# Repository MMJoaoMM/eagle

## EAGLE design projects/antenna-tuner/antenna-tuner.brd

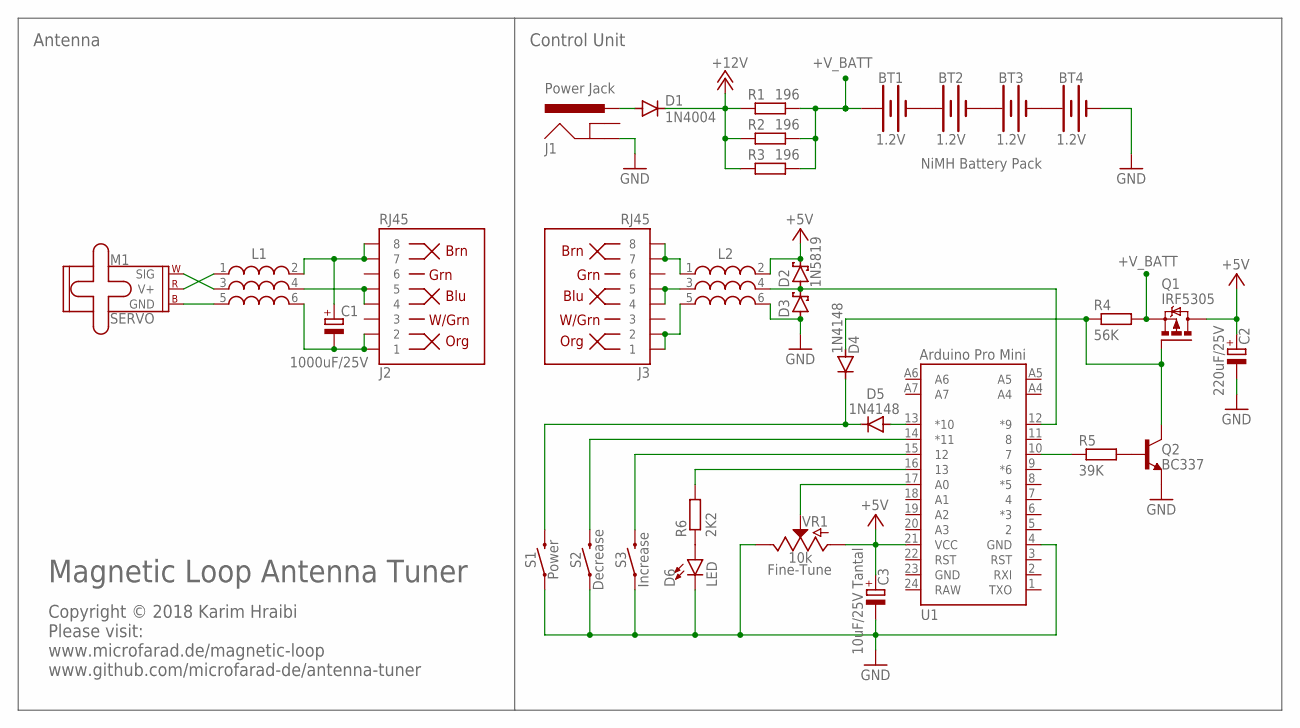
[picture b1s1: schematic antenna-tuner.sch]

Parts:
BT1, BT2, BT3, BT4: 1.2V; BATTERY-AA
C1: 1000uF/25V; E5-10,5
C2: 220uF/25V; E2,5-6
C3: 10uF/25V Tantal; E2,5-6
D1: 1N4004; DO41-10
D2, D3: 1N5819; DO41-7.6
D4, D5: 1N4148; DO35-7
D6: LED; LED_5MM
J1: Power Jack; POWER_JACK_PTH_BREAD
J2, J3: RJ45; RJ45-8
L1, L2: WE-MLS-3WAY_74273001; WE-3WAY_74273001
M1: SERVO; 1X03
Q1: IRF5305; TO220V
Q2: BC337; TO92
R1, R2, R3: 196; 0207/7
R4: 56K; 0207/7
R5: 39K; 0207/7
R6: 2K2; 0207/7
S1: Power; TACTILE_SWITCH_PTH_6.0MM
S2: Decrease; TACTILE_SWITCH_PTH_6.0MM
S3: Increase; TACTILE_SWITCH_PTH_6.0MM
U1: Arduino Pro Mini; ARDUINO_PRO_MINI_TS
VR1: 10k; POT-PTH-ALPS

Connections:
+5V: C2.+, C3.+, D2.C, L2.2, Q1.2, U1.21 (VCC), VR1.P$3 (A)
+12V: D1.C, R1.1, R2.1, R3.1
+V_BATT: BT1.PWR@1 (+), Q1.3, R1.2, R2.2, R3.2, R4.2
GND: BT4.GND@1 (-), C2.-, C3.-, D3.A, D6.K (C), J1.GND, L2.6, Q2.1 (E), S1.1, S2.1, S3.1, U1.4 (GND), U1.23 (GND), VR1.P$1 (E)
unnamed: D1.A, J1.PWR
unnamed: BT1.GND@1 (-), BT2.PWR@1 (+)
unnamed: BT3.GND@1 (-), BT4.PWR@1 (+)
unnamed: BT2.GND@1 (-), BT3.PWR@1 (+)
unnamed: U1.17 (A0), VR1.P$2 (S)
unnamed: Q2.2 (B), R5.1, R5.2, U1.10 (7)
unnamed: D6.A, R6.1
unnamed: D4.A, Q1.1, Q2.3 (C), R4.1
unnamed: R6.2, U1.16 (13)
unnamed: S3.3 (2), U1.15 (12)
unnamed: S2.3 (2), U1.14 (*11)
unnamed: D5.A, U1.13 (*10)
unnamed: D4.C, D5.C, S1.3 (2)
unnamed: D2.A, D3.C, L2.4, U1.12 (*9)
unnamed: J3.1, J3.2, L2.5
unnamed: J3.7, J3.8, L2.1
unnamed: J3.4, J3.5, L2.3
unnamed: C1.+, J2.7, J2.8, L1.2
unnamed: J2.4, J2.5, L1.4
unnamed: C1.-, J2.1, J2.2, L1.6
unnamed: L1.1, M1.2 (V+)
unnamed: L1.5, M1.3 (GND)
unnamed: L1.3, M1.1 (SIG)
RAW: U1.24 (RAW)

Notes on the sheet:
Magnetic Loop Antenna Tuner
Copyright © 2018 Karim Hraibi Please visit: www.microfarad.de/magnetic-loop www.github.com/microfarad-de/antenna-tuner
Fine-Tune
NiMH Battery Pack
Control Unit
Antenna

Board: 2 copper layers, 32 parts (0 on the bottom side), 27 nets, no tracks yet.

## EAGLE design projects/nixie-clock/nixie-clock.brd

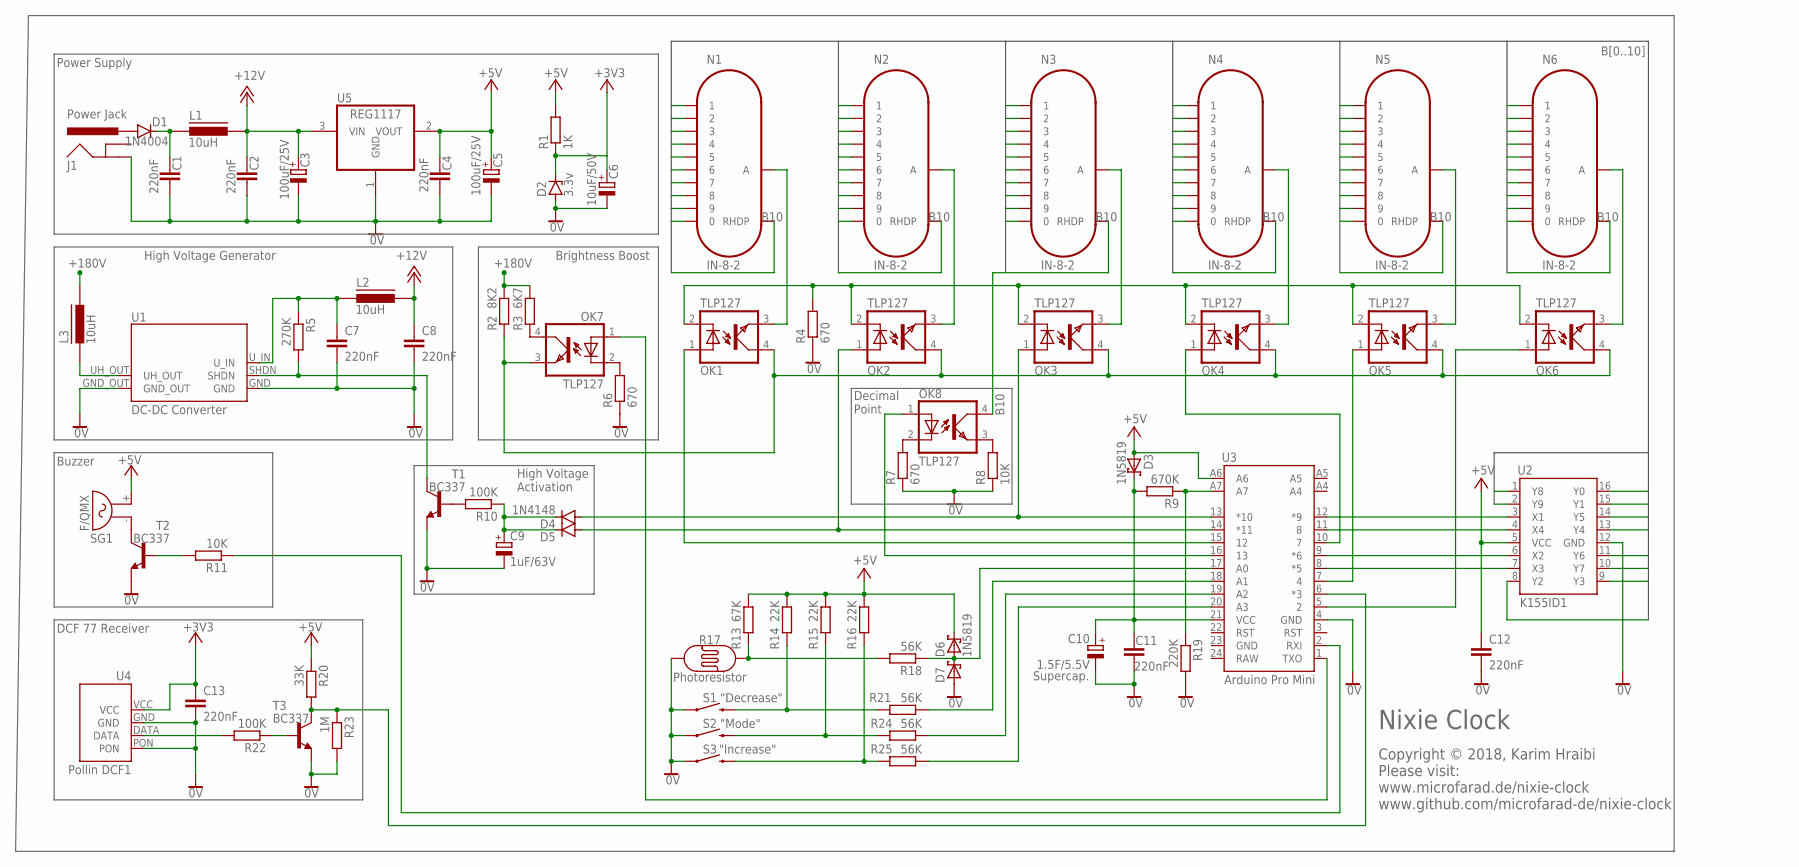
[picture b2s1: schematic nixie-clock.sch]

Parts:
C1, C2, C4, C7, C8, C11, C12, C13: 220nF; C025-024X044
C3, C5: 100uF/25V; E2,5-6
C6: 10uF/50V; E2-4
C9: 1uF/63V; E1,8-4
C10: 1.5F/5.5V; SUPERCAP/1.5F/5.5V
D1: 1N4004; DO41-10
D2: 3.3v; ZDIO-5
D3, D6: 1N5819; DO41-7.6
D4, D5: 1N4148; DO35-7
D7: 1N5819-B; DO41-7.6
J1: Power Jack; POWER_JACK_SLOT
L1, L2, L3: 10uH; CHOKE/9.5MM
N1, N2, N3, N4, N5, N6: IN-8-2
OK1, OK2, OK3, OK4, OK5, OK6, OK7, OK8: TLP127; MINI-FLAT-4
R1: 1K; 0207/7
R2: 8K2; 0207/7
R3: 6K7; 0207/7
R4, R6, R7: 670; 0207/7
R5: 270K; 0207/7
R8, R11: 10K; 0207/7
R9: 670K; 0207/7
R10, R22: 100K; 0207/7
R13: 67K; 0207/7
R14, R15, R16: 22K; 0207/7
R17: Photoresistor; PHOTOCELL
R18, R21, R24, R25: 56K; 0207/7
R19: 220K; 0207/7
R20: 33K; 0207/7
R23: 1M; 0207/7
S1: "Decrease"; TACTILE_SWITCH_PTH_6.0MM
S2: "Mode"; TACTILE_SWITCH_PTH_6.0MM
S3: "Increase"; TACTILE_SWITCH_PTH_6.0MM
SG1: F/QMX
T1, T2, T3: BC337; TO92
U1: DC-DC Converter; CHINA_HV_DC_DC
U2: K155ID1; DIL16
U3: Arduino Pro Mini; ARDUINO_PRO_MINI_TS
U4: Pollin DCF1; DCF1
U5: REG1117; SOT223

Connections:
0V: C1.2, C2.2, C3.-, C4.2, C5.-, C6.-, C7.2, C8.2, C9.-, C10.-, C11.2, C12.2, C13.2, D2.A, D7.A, J1.GND@2 (GND), R4.1, R6.1, R7.1, R8.1, R17.1, R19.2, R23.2, S1.1, S2.1, S3.1, T1.1 (E), T2.1 (E), T3.1 (E), U1.GND, U1.GND_OUT, U2.12 (GND), U3.4 (GND), U4.GND, U4.PON, U5.1 (GND)
180VRAW: L3.1, U1.UH_OUT
+3V3: C6.+, C13.1, D2.C, R1.1, U4.VCC
+5V: C4.1, C5.+, C12.1, D3.A, D6.C, R1.2, R13.1, R14.1, R15.1, R16.1, R20.1, SG1.+ (2), U2.5 (VCC), U3.A6, U5.2 (VOUT)
+12V: C2.1, C3.+, C8.1, L1.2, L2.2, U5.3 (VIN)
+180V: L3.2, R2.2, R3.2
B0: N1.0, N2.0, N3.0, N4.0, N5.0, N6.0, U2.16 (Y0)
B1: N1.1, N2.1, N3.1, N4.1, N5.1, N6.1, U2.15 (Y1)
B2: N1.2, N2.2, N3.2, N4.2, N5.2, N6.2, U2.8 (Y2)
B3: N1.3, N2.3, N3.3, N4.3, N5.3, N6.3, U2.9 (Y3)
B4: N1.4, N2.4, N3.4, N4.4, N5.4, N6.4, U2.13 (Y4)
B5: N1.5, N2.5, N3.5, N4.5, N5.5, N6.5, U2.14 (Y5)
B6: N1.6, N2.6, N3.6, N4.6, N5.6, N6.6, U2.11 (Y6)
B7: N1.7, N2.7, N3.7, N4.7, N5.7, N6.7, U2.10 (Y7)
B8: N1.8, N2.8, N3.8, N4.8, N5.8, N6.8, U2.1 (Y8)
B9: N1.9, N2.9, N3.9, N4.9, N5.9, N6.9, U2.2 (Y9)
B10: N1.. (RHDP), N2.. (RHDP), N3.. (RHDP), N4.. (RHDP), N5.. (RHDP), N6.. (RHDP), OK8.4 (COL)
GND: U3.23 (GND)
unnamed: N6.A, OK6.3 (EMIT)
unnamed: N5.A, OK5.3 (EMIT)
unnamed: N4.A, OK4.3 (EMIT)
unnamed: N3.A, OK3.3 (EMIT)
unnamed: N2.A, OK2.3 (EMIT)
unnamed: N1.A, OK1.3 (EMIT)
unnamed: OK1.4 (COL), OK2.4 (COL), OK3.4 (COL), OK4.4 (COL), OK5.4 (COL), OK6.4 (COL), OK7.3 (EMIT), R2.1
unnamed: OK7.4 (COL), R3.1
unnamed: OK6.1 (A), U3.5 (2)
unnamed: OK5.1 (A), U3.7 (4)
unnamed: OK4.1 (A), U3.10 (7)
unnamed: D4.A, OK3.1 (A), U3.13 (*10)
unnamed: D5.A, OK2.1 (A), U3.14 (*11)
unnamed: OK1.1 (A), U3.15 (12)
unnamed: C7.1, L2.1, R5.1, U1.U_IN
unnamed: R10.2, T1.2 (B)
unnamed: C9.+, D4.C, D5.C, R10.1
unnamed: R5.2, T1.3 (C), U1.SHDN
unnamed: OK1.2 (C), OK2.2 (C), OK3.2 (C), OK4.2 (C), OK5.2 (C), OK6.2 (C), R4.2
unnamed: OK7.2 (C), R6.2
unnamed: OK7.1 (A), U3.1 (TXO)
unnamed: OK8.3 (EMIT), R8.2
unnamed: OK8.2 (C), R7.2
unnamed: OK8.1 (A), U3.16 (13)
unnamed: D1.A, J1.PWR
unnamed: C1.1, D1.C, L1.1
unnamed: R20.2, R23.1, T3.3 (C), U3.6 (*3)
unnamed: R11.2, T2.2 (B)
unnamed: R22.1, T3.2 (B)
unnamed: R22.2, U4.DATA
unnamed: SG1.- (1), T2.3 (C)
unnamed: R11.1, U3.2 (RXI)
unnamed: C10.+, C11.1, D3.C, R9.2, U3.21 (VCC)
unnamed: R9.1, R19.1, U3.A7
unnamed: D6.A, D7.C, R18.1, U3.17 (A0)
unnamed: R13.2, R17.2, R18.2
unnamed: R14.2, R21.2, S1.3 (2)
unnamed: R15.2, R24.2, S2.3 (2)
unnamed: R16.2, R25.2, S3.3 (2)
unnamed: R21.1, U3.18 (A1)
unnamed: R24.1, U3.19 (A2)
unnamed: R25.1, U3.20 (A3)
RAW: U3.24 (RAW)
X1: U2.3 (X1), U3.12 (*9)
X2: U2.6 (X2), U3.9 (*6)
X3: U2.7 (X3), U3.8 (*5)
X4: U2.4 (X4), U3.11 (8)

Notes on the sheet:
Supercap.
DCF 77 Receiver
Buzzer
High Voltage Generator
Power Supply
Brightness Boost
High Voltage Activation
Decimal Point
Nixie Clock
Copyright © 2018, Karim Hraibi Please visit: www.microfarad.de/nixie-clock www.github.com/microfarad-de/nixie-clock

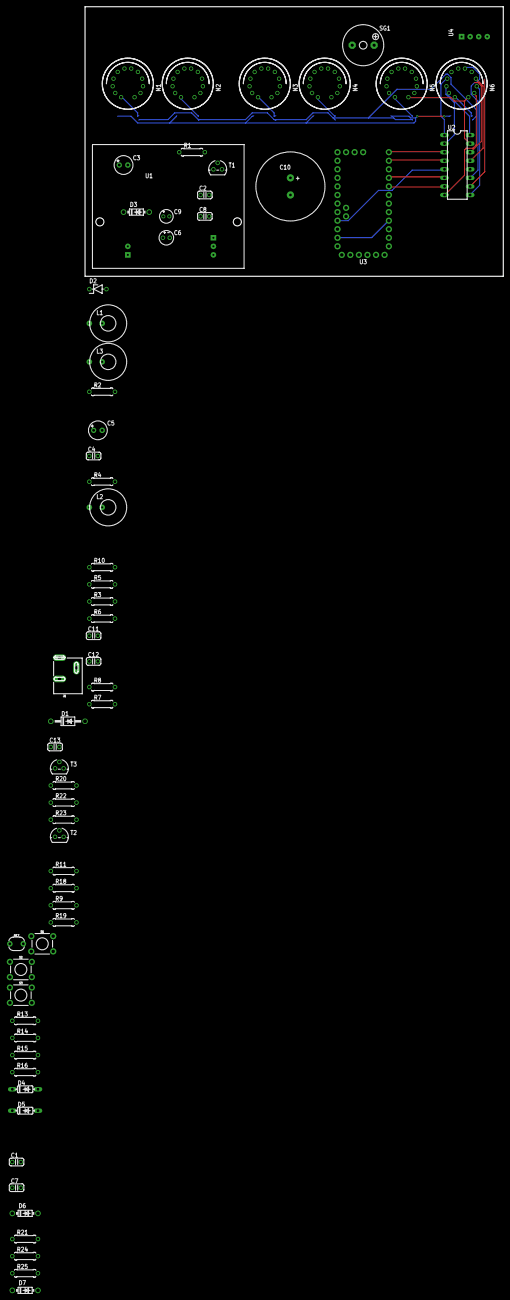
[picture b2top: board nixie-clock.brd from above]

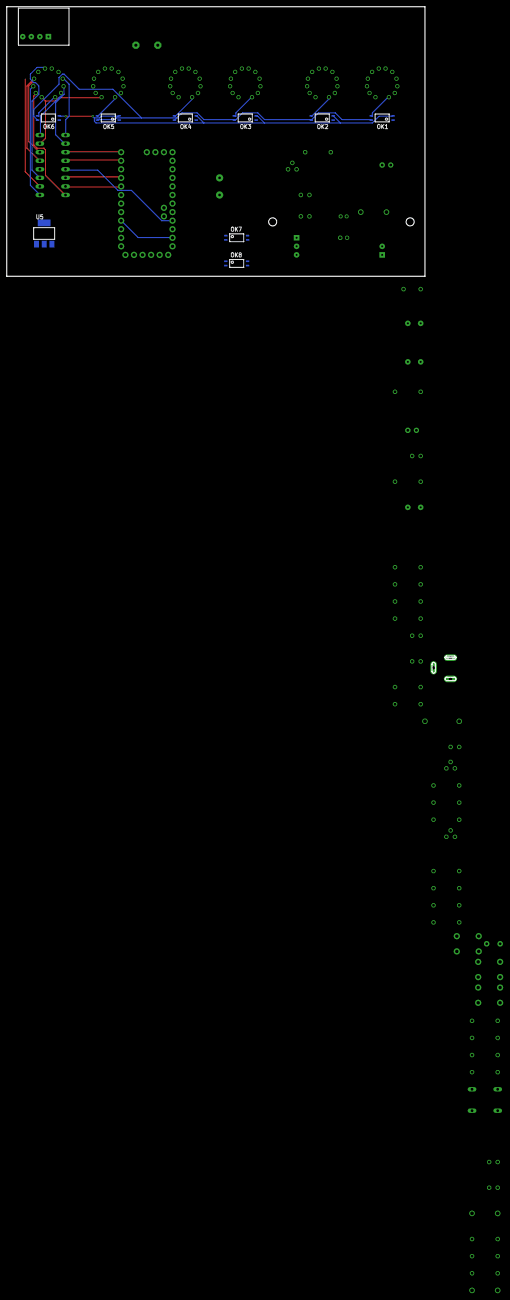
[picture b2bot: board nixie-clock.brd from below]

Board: 2 copper layers, 74 parts (9 on the bottom side), 63 nets.

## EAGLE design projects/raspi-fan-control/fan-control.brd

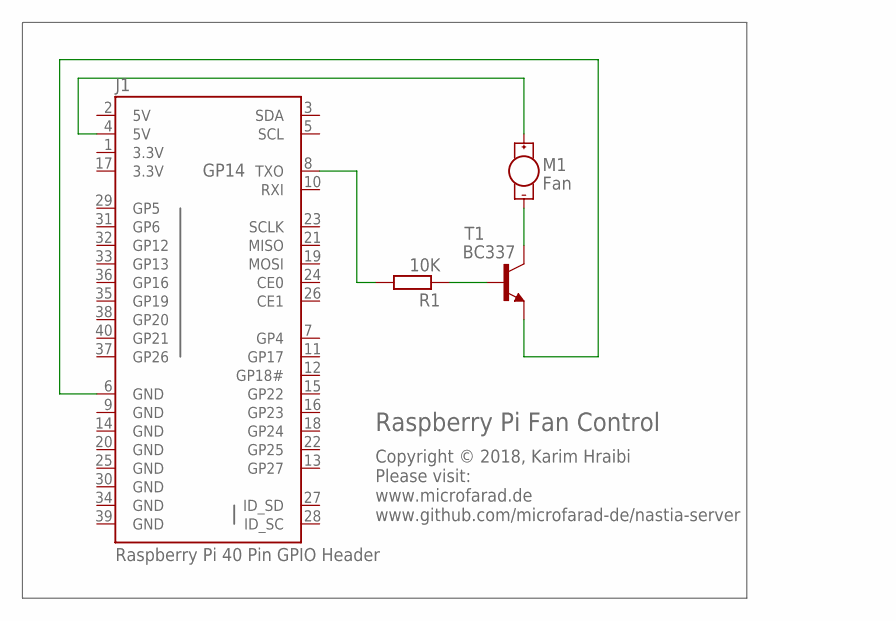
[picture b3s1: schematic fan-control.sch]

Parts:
J1: Raspberry Pi 40 Pin GPIO Header; 2X20
M1: Fan; VIBE-MOTOR-10MM
R1: 10K; 0207/7
T1: BC337; TO92

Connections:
3.3V: J1.1 (3.3V), J1.17 (3.3V)
5V: J1.2 (5V)
GND: J1.9 (GND), J1.14 (GND), J1.20 (GND), J1.25 (GND), J1.30 (GND), J1.34 (GND), J1.39 (GND)
GP14: J1.8 (TXO), R1.2
unnamed: R1.1, T1.2 (B)
unnamed: M1.-, T1.3 (C)
unnamed: J1.4 (5V), M1.+
unnamed: J1.6 (GND), T1.1 (E)

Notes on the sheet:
Raspberry Pi Fan Control
Copyright © 2018, Karim Hraibi Please visit: www.microfarad.de www.github.com/microfarad-de/nastia-server

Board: 2 copper layers, 4 parts (0 on the bottom side), 7 nets, no tracks yet.

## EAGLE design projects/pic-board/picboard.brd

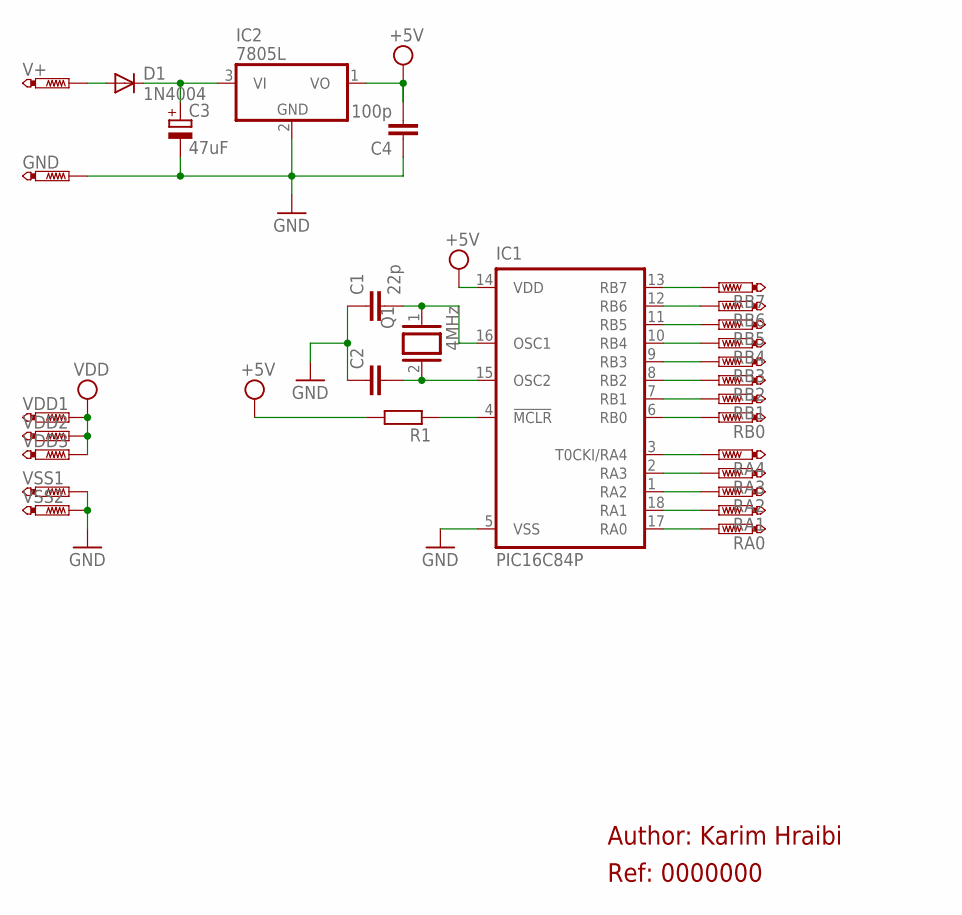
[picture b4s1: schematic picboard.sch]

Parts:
C1: 22p; C025-025X050
C2: C-EU025-025X050; C025-025X050
C3: 47uF; E2,5-5
C4: 100p; C025-025X050
D1: 1N4004; DO41-10
GND: PTR1PAD1; P1
IC1: PIC16C84P; DIL18
IC2: 7805L; TO92
Q1: 4MHz; QS
R1: R-EU_0207/2V; 0207/2V
RA0, RA1, RA2, RA3, RA4: PTR1PAD1; P1
RB0, RB1, RB2, RB3, RB4, RB5, RB6, RB7: PTR1PAD1; P1
V+: PTR1PAD1; P1
VDD1, VDD2, VDD3: PTR1PAD1; P1
VSS1, VSS2: PTR1PAD1; P1

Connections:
GND: C1.1, C2.1, C3.-, C4.1, GND.P$1, IC1.5 (VSS), IC2.2 (GND), VSS1.P$1, VSS2.P$1
unnamed: C2.2, IC1.15 (OSC2), Q1.2
unnamed: C1.2, IC1.16 (OSC1), Q1.1
unnamed: IC1.13 (RB7), RB7.P$1
unnamed: IC1.12 (RB6), RB6.P$1
unnamed: IC1.11 (RB5), RB5.P$1
unnamed: IC1.10 (RB4), RB4.P$1
unnamed: IC1.9 (RB3), RB3.P$1
unnamed: IC1.8 (RB2), RB2.P$1
unnamed: IC1.7 (RB1), RB1.P$1
unnamed: IC1.6 (RB0), RB0.P$1
unnamed: IC1.3 (T0CKI/RA4), RA4.P$1
unnamed: IC1.2 (RA3), RA3.P$1
unnamed: IC1.1 (RA2), RA2.P$1
unnamed: IC1.18 (RA1), RA1.P$1
unnamed: IC1.17 (RA0), RA0.P$1
unnamed: IC1.4 (!MCLR), R1.1
unnamed: D1.A, V+.P$1
unnamed: C3.+, D1.C, IC2.3 (VI)
VDD: C4.2, IC1.14 (VDD), IC2.1 (VO), R1.2, VDD1.P$1, VDD2.P$1, VDD3.P$1

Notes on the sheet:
Author: Karim Hraibi
Ref: 0000000

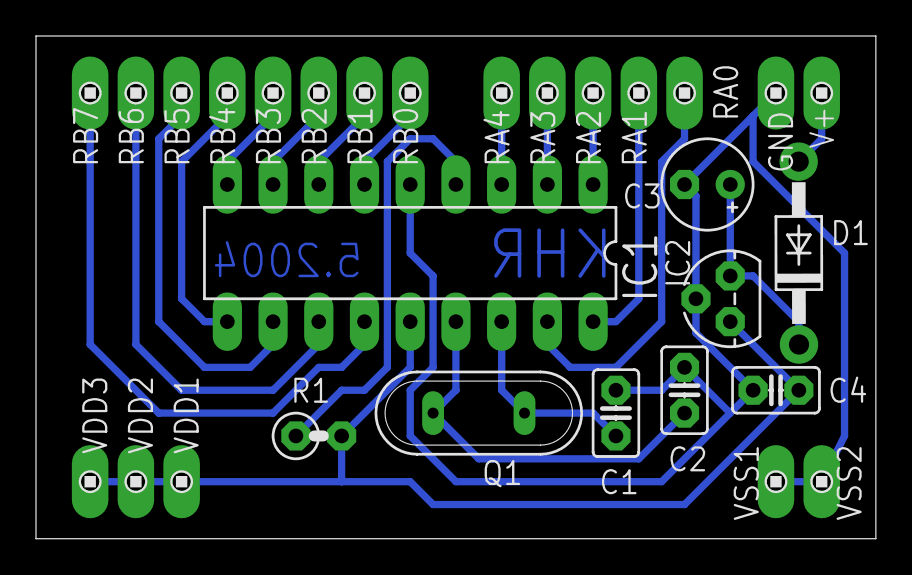
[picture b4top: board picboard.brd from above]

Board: 2 copper layers, 46.7 x 27.9 mm, 29 parts (0 on the bottom side), 20 nets.

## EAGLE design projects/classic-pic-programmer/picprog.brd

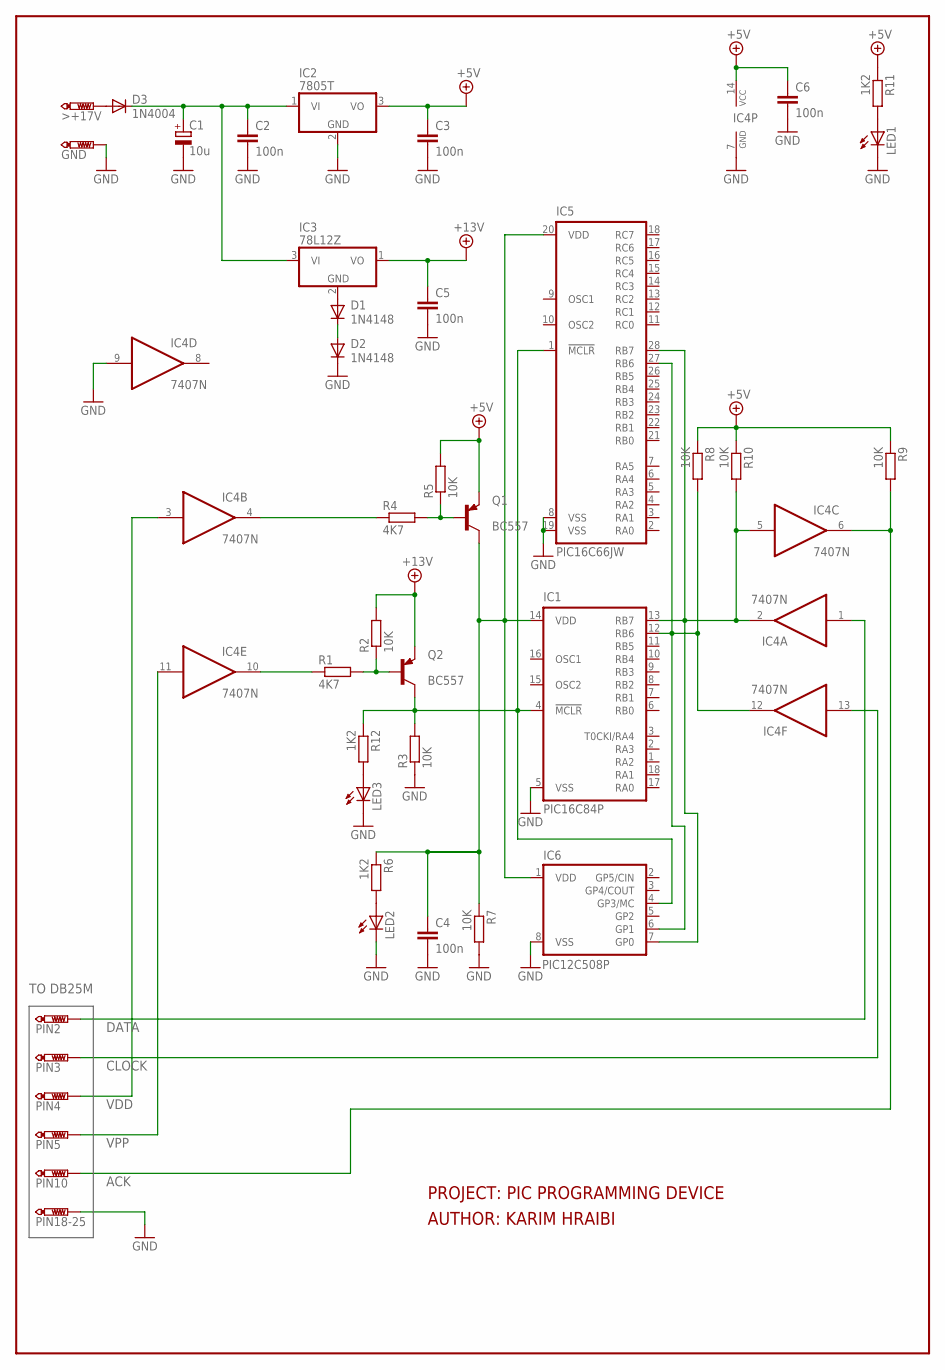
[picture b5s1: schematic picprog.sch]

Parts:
>+17V: PTR1PAD1; P1
C1: 10u; E2,5-7
C2, C3, C4, C5, C6: 100n; C025-025X050
D1, D2: 1N4148; DO35-10
D3: 1N4004; DO41-10
GND: PTR1PAD1; P1
IC1: PIC16C84P; DIL18
IC2: 7805T; TO220H
IC3: 78L12Z; TO92
IC4: 7407N; DIL14
IC5: PIC16C66JW; DIL28-6
IC6: PIC12C508P; DIL8
LED1, LED2, LED3: LED5MM
PIN2, PIN3, PIN4, PIN5, PIN10, PIN18-25: PTR1PAD1; P1
Q1, Q2: BC557; TO92
R1: 4K7; 0207/12
R2, R3, R5, R7, R8, R10: 10K; 0207/12
R4: 4K7; 0207/15
R6, R11, R12: 1K2; 0207/12
R9: 10K; 0207/15

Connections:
+5V: C3.1, C6.1, IC2.3 (VO), IC4.14 (VCC), Q1.1 (E), R5.2, R8.1, R9.1, R10.1, R11.1
+12V: C5.1, IC3.1 (VO), Q2.1 (E), R2.2
ACK: IC4.6 (O), PIN10.P$1, R9.2
CLOCK: IC4.13 (I), PIN3.P$1
DATA: IC4.1 (I), PIN2.P$1
GND: C1.-, C2.2, C3.2, C4.2, C5.2, C6.2, D2.C, GND.P$1, IC1.5 (VSS), IC2.2 (GND), IC4.7 (GND), IC4.9 (I), IC5.8 (VSS), IC5.19 (VSS), IC6.8 (VSS), LED1.K (C), LED2.K (C), LED3.K (C), PIN18-25.P$1, R3.1, R7.2
unnamed: D1.A, IC3.2 (GND)
unnamed: D1.C, D2.A
unnamed: >+17V.P$1, D3.A
unnamed: C1.+, C2.1, D3.C, IC2.1 (VI), IC3.3 (VI)
unnamed: IC1.4 (!MCLR), IC5.1 (!MCLR), IC6.4 (GP3/MC), Q2.3 (C), R3.2, R12.1
unnamed: IC4.10 (O), R1.1
unnamed: Q1.2 (B), R4.2, R5.1
unnamed: Q2.2 (B), R1.2, R2.1
unnamed: IC1.13 (RB7), IC4.2 (O), IC4.5 (I), IC5.28 (RB7), IC6.7 (GP0), R10.2
unnamed: IC4.4 (O), R4.1
unnamed: C4.1, IC1.14 (VDD), IC5.20 (VDD), IC6.1 (VDD), Q1.3 (C), R6.1, R7.1
unnamed: LED1.A, R11.2
unnamed: IC1.12 (RB6), IC4.12 (O), IC5.27 (RB6), IC6.6 (GP1), R8.2
unnamed: LED2.A, R6.2
unnamed: LED3.A, R12.2
VDD: IC4.3 (I), PIN4.P$1
VPP: IC4.11 (I), PIN5.P$1

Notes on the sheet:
AUTHOR: KARIM HRAIBI
TO DB25M
PROJECT: PIC PROGRAMMING DEVICE

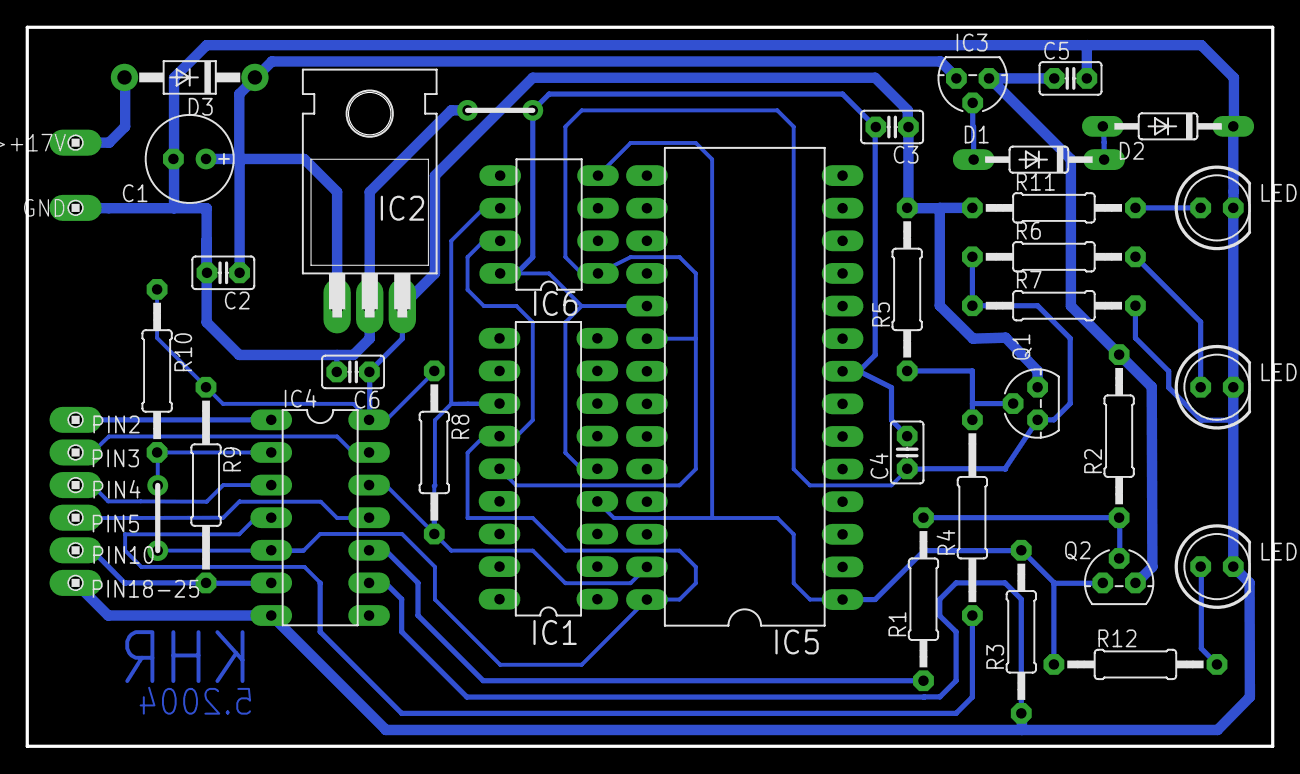
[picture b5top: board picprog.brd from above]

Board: 2 copper layers, 97.0 x 56.0 mm, 40 parts (0 on the bottom side), 23 nets.

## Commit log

2018-12-14 Initial import
2018-12-15 Update nixie-clock
2018-12-15 Finalized circuit diagram
2018-12-15 Renumber parts
2018-12-15 Added copyright notice
2018-12-16 Update schematic
2018-12-18 Update nixie-clock schematic
2018-12-19 Add Raspberry Pi fan control schematic
2018-12-20 Rename folder
2018-12-23 Created schematic for the antenna tuner
2018-12-23 Updated antenna tuner schematic
2018-12-24 Update copyright notice
2018-12-24 Added pi-server HDD cable schematic
    Renamed project to pi-server
2018-12-27 Added .epf files
2018-12-31 Added li-charger
2019-01-13 Updated schematic
2019-02-01 Remove .brd files
2019-02-02 updated li-charger schematic
2019-03-10 updated nixie clock
2019-06-23 Updated li-charger
2019-06-24 Updated li-charger.sch

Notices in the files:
parts and their libraries:
SparkFun-Connectors: Licensing: Creative Commons ShareAlike 4.0 International - https://creativecommons.org/licenses/by-sa/4.0
Wurth_Elektronik_Passive_rev18f: Copyright: Würth Elektronik
